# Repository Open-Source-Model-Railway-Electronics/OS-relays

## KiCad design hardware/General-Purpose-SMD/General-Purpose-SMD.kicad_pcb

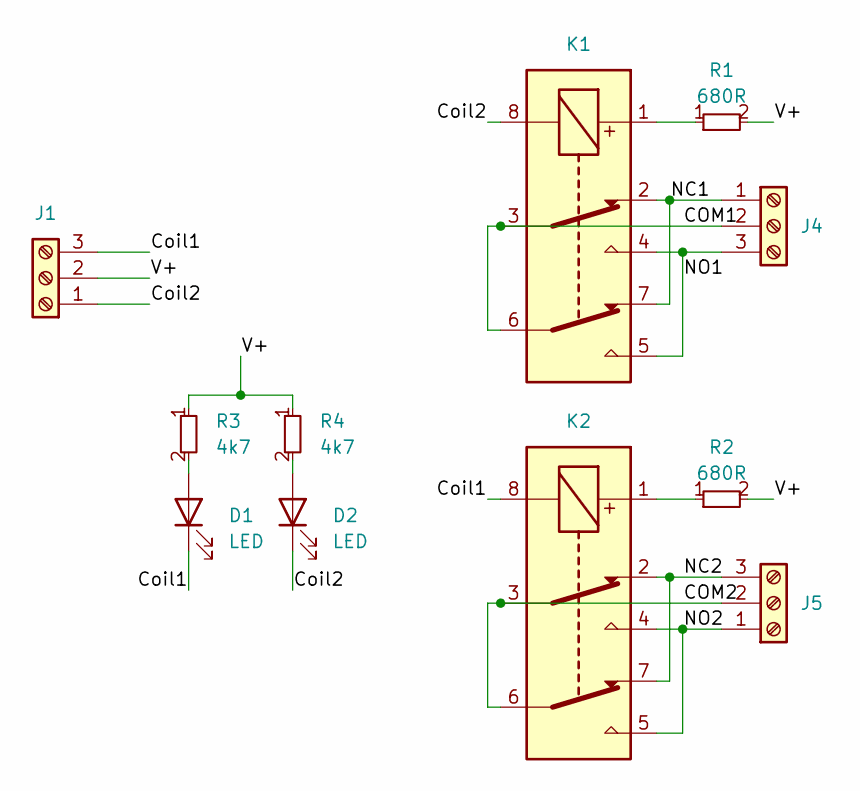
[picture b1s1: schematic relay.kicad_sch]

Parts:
D1, D2: LED; LED_0805_2012Metric_Pad1.15x1.40mm_HandSolder; JLCPCB Part# C2296
J1: Screw_Terminal_01x03; connector_3.50mm_3P horizontal_MALE; JLCPCB Part# C6394074
J4: Screw_Terminal_01x03; PhoenixContact_MC_1,5_3-G-3.5_1x03_P3.50mm_Horizontal; JLCPCB Part# C22380440
J5: Screw_Terminal_01x03; PhoenixContact_MCV_1,5_3-G-3.5_1x03_P3.50mm_Vertical; Mating Part# C560231; JLCPCB Part# C192778
K1, K2: G6K-2F-Y-TR DC12; Relay_DPDT_Omron_G6K-2F-Y; JLCPCB Part# C397192
R1, R2: 680R; R_0603_smalltext; JLCPCB Part# C17798
R3, R4: 4k7; R_0603_smalltext; JLCPCB Part# C23162

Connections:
/relay1/COM1: J4.2, K1.3, K1.6
/relay1/COM2: J5.2, K2.3, K2.6
/relay1/Coil1: D1.1 (K), J1.3, K2.8
/relay1/Coil2: D2.1 (K), J1.1, K1.8
/relay1/NC1: J4.1, K1.2, K1.7
/relay1/NC2: J5.3, K2.2, K2.7
/relay1/NO1: J4.3, K1.4, K1.5
/relay1/NO2: J5.1, K2.4, K2.5
/relay1/V+: J1.2, R1.2, R2.2, R3.1, R4.1
unnamed: D1.2 (A), R3.2
unnamed: D2.2 (A), R4.2
unnamed: K1.1, R1.1
unnamed: K2.1, R2.1

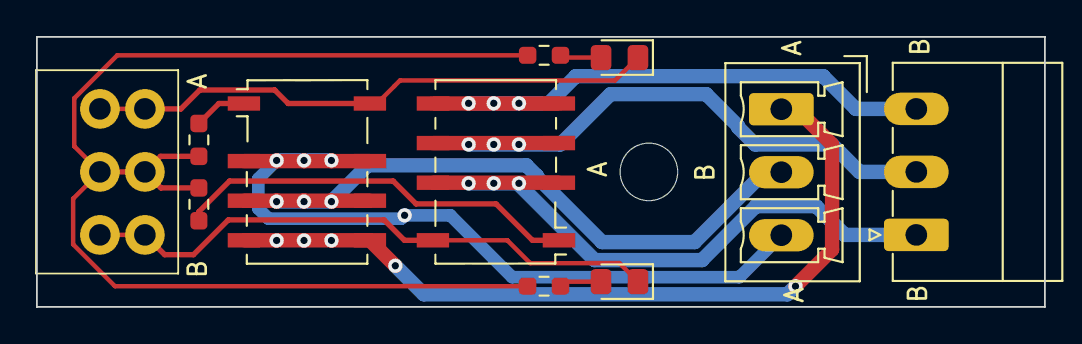
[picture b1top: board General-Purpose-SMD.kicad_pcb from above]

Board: 2 copper layers, 56.0 x 15.0 mm, 11 parts (0 on the bottom side), 13 nets.

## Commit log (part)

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2026-05-24 added translations
2026-05-25 added images
2026-05-30 added picture
